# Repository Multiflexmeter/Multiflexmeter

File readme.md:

# Multiflexmeter V4
Frequent, low-cost and flexible measurements using the MultiFlexMeter. An Open-Source sensor platform.

## Documentation

- [Firmware Documentation](https://multiflexmeter.github.io/multiflexmeter)
- [Hardware specification](./docs/P22296-1-SPEC-2.0.pdf)
- [Firmware specification](./docs/P22296-10-SPEC-2.0.pdf)

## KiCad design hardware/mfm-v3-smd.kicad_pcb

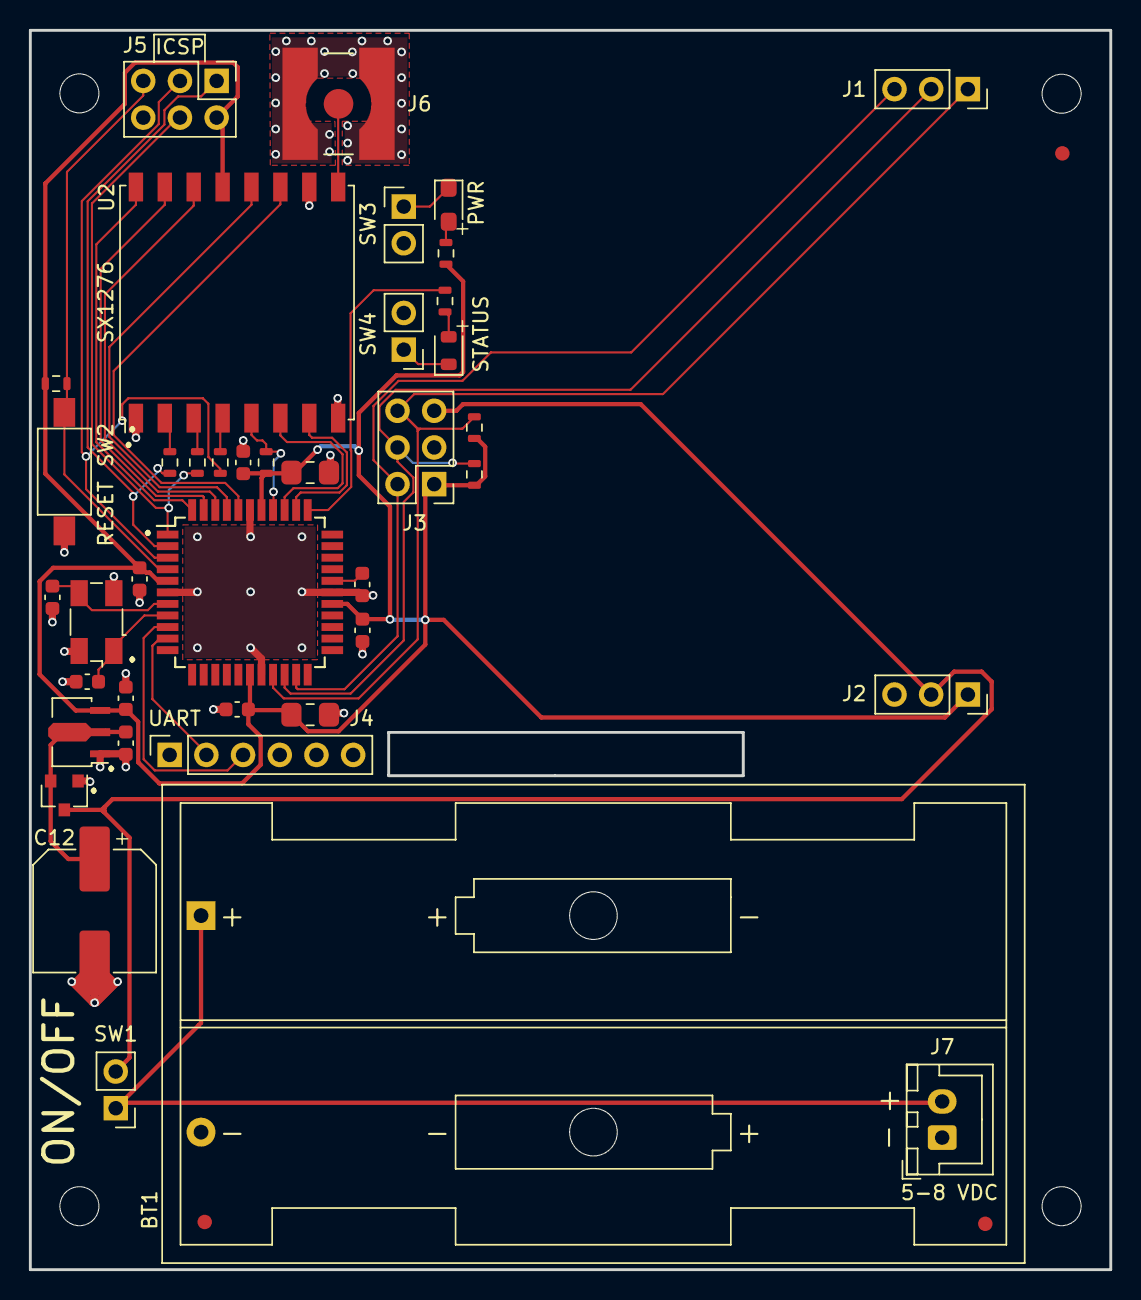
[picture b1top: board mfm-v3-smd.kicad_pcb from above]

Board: 2 copper layers, 74.8 x 85.8 mm, 47 parts (0 on the bottom side), 34 nets.

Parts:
BT1: Battery; BatteryHolder_Keystone_2462_2xAA
C1, C2: 2.2uF; C_0603_1608Metric
C3, C4, C6, C9, C11: 100nF; C_0603_1608Metric
C5, C10: 10uF; C_0805_2012Metric_GRM21BR61E106MA73L
C7, C8: 10pF; C_0603_1608Metric
C12: 820uF 16v; C_Elec_8x10.2
D1: LED_PWR; LED_0805_2012Metric_APT2012LSECK
D2: LED_STAT; LED_0805_2012Metric_APTD2012LQBC-D
FID1, FID2, FID3: Fiducial; Fiducial_1mm_Mask2mm
H1, H2, H3, H4: MountingHole; MountingHole_2.7mm_M2.5_DIN965
J1: MFM Module-Left; MFM_Module_Board_P123
J2: MFM Module-Right; PinSocket_1x03_P2.54mm_Vertical
J3: SMBUS Connector; PinHeader_2x03_P2.54mm_Vertical
J4: FTDI Connector; PinSocket_1x06_P2.54mm_Vertical
J5: ICSP Connector; PinHeader_2x03_P2.54mm_Vertical
J6: Antenna; LINX_CONSMA001-SMD-G
J7: JST Jack; JST_XH_B2B-XH-A_1x02_P2.50mm_Vertical
Q1: R.V. Protect; SOT-23
R1: 750R; R_0603_1608Metric_CRCW...C
R2, R5, R7, R8: 324R; R_0603_1608Metric_CRCW...C
R3, R4: 10k; R_0603_1608Metric_CRCW...C
R6, R9: 4k7; R_0603_1608Metric_CRCW...C
SW1: SW_VBAT; PinHeader_1x02_P2.54mm_Vertical
SW2: RESET; SW_SPST_PTS636
SW3: SW_LED_PWR; PinHeader_1x02_P2.54mm_Vertical
SW4: SW_LED_STAT; PinHeader_1x02_P2.54mm_Vertical
U1: MCP1703A-3302_SOT89; SOT-89-3_MCP1703
U2: LoRa_Radio; HOPERF_RFM9XW_SMD
U3: ATmega1284P-AU; TQFP-44_10x10mm_P0.8mm
Y1: 8MHz; Crystal_SMD_Abracon_ABM3B-4Pin_5.0x3.2mm

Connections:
+3V3: C2.2, C3.2, C4.2, C5.2, C6.2, C9.2, C10.1, J2.1, J3.1, J5.2, R1.1, R3.2, R4.2, R6.2, R9.2, U1.3, U2.13, U3.5, U3.17, U3.27, U3.38
AVR_MISO: J5.1, R8.1, U3.2
AVR_MOSI: J5.4, R7.1, U3.1
AVR_RX0: J4.3, U3.9
AVR_SCK: J5.3, R5.1, U3.3
AVR_TX0: J4.2, U3.10
GND: BT1.2, C1.1, C2.1, C3.1, C4.1, C5.1, C6.1, C7.1, C8.1, C9.1, C10.2, C11.1, C12.2, J2.3, J3.3, J4.6, J5.6, J6.2, J7.1, Q1.1, SW2.2, SW3.2, SW4.2, U1.1, U2.1, U2.8, U2.10, U3.6, U3.18, U3.28, U3.39, Y1.2, Y1.4
I2C_SCL: J1.1, J3.6, R9.1, U3.19
I2C_SDA: J1.2, J3.4, R6.1, U3.20
LED_STAT: R2.1, U3.34
NRST: J5.5, R4.1, SW2.1, U3.4
unnamed: BT1.1, J7.2, SW1.1
unnamed: C1.2, C12.1, Q1.2, U1.2
unnamed: C11.2, U3.29
unnamed: D1.1, SW3.1
unnamed: D1.2, R1.2
unnamed: D2.1, SW4.1
unnamed: D2.2, R2.2
unnamed: J6.1, U2.9
RADIO_DIO0: U2.14, U3.42
RADIO_DIO1: U2.15, U3.43
RADIO_DIO2: U2.16, U3.44
RADIO_DIO3: U2.11, U3.40
RADIO_DIO4: U2.12, U3.41
RADIO_DIO5: U2.7, U3.35
RADIO_NSS: R3.1, U2.5, U3.37
RADIO_RST: U2.6, U3.36
SMBALERT: J1.3, J3.2, U3.21
SPI_MISO: R8.2, U2.2
SPI_MOSI: R7.2, U2.3
SPI_SCK: R5.2, U2.4
VBAT: J2.2, J3.5, Q1.3, SW1.2
XTAL1: C7.2, U3.8, Y1.1
XTAL2: C8.2, U3.7, Y1.3

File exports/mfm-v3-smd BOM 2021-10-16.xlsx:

mfm-v3-smd
Quantity | Designator | Value | Footprint | Manufacturer | Manufacturer #
1 | BT1 | Battery | Battery:BatteryHolder_Keystone_2462_2xAA | Keystone | 2462
1 | C1 | 2.2uF | Capacitor_SMD:C_0603_1608Metric | TDK | C1608X7R1A225K080AE
1 | C2 | 2.2uF | Capacitor_SMD:C_0603_1608Metric | TDK | C1608X7R1A225K080AE
1 | C3 | 100nF | Capacitor_SMD:C_0603_1608Metric | TDK | C1608X7R1E104K080AA
1 | C4 | 100nF | Capacitor_SMD:C_0603_1608Metric | TDK | C1608X7R1E104K080AA
1 | C5 | 10uF | Capacitor_SMD:C_0805_2012Metric_GRM21BR61E106MA73L | Murata | GRM21BR61E106MA73L
1 | C6 | 100nF | Capacitor_SMD:C_0603_1608Metric | TDK | C1608X7R1E104K080AA
1 | C7 | 10pF | Capacitor_SMD:C_0603_1608Metric | Murata | GRT0335C1E100GA02D
1 | C8 | 10pF | Capacitor_SMD:C_0603_1608Metric | Murata | GRT0335C1E100GA02D
1 | C9 | 100nF | Capacitor_SMD:C_0603_1608Metric | TDK | C1608X7R1E104K080AA
1 | C10 | 10uF | Capacitor_SMD:C_0805_2012Metric_GRM21BR61E106MA73L | Murata | GRM21BR61E106MA73L
1 | C11 | 100nF | Capacitor_SMD:C_0603_1608Metric | TDK | C1608X7R1E104K080AA
1 | C12 | 820uF 16v | Capacitor_SMD:C_Elec_8x10.2 | <niet bestucken> | <niet bestucken>
1 | D1 | LED_PWR | custom_library_FP:LED_0805_2012Metric_APT2012LSECK | Kingbright | APT2012LSECK/J3-PRV
1 | D2 | LED_STAT | custom_library_FP:LED_0805_2012Metric_APTD2012LQBC-D | Kingbright | APTD2012LQBC/D
1 | J1 | MFM Module-Left | custom_library_FP:MFM_Module_Board_P123 | Preci-dip | 801-87-003-10-005101
1 | J2 | MFM Module-Right | Connector_PinSocket_2.54mm:PinSocket_1x03_P2.54mm_Vertical | Preci-dip | 801-87-003-10-005101
1 | J3 | SMBUS Connector | Connector_PinHeader_2.54mm:PinHeader_2x03_P2.54mm_Vertical | Preci-dip | 892-18-006-10-002101
1 | J4 | FTDI Connector | Connector_PinSocket_2.54mm:PinSocket_1x06_P2.54mm_Vertical | Preci-dip | 801-87-006-10-001101
1 | J5 | ICSP Connector | Connector_PinHeader_2.54mm:PinHeader_2x03_P2.54mm_Vertical | Preci-dip | 892-18-006-10-002101
1 | J6 | Antenna | custom_library_FP:LINX_CONSMA001-SMD-G | Linx Technologies | CONSMA001-SMD-G-T
1 | J7 | JST Jack | Connector_JST:JST_XH_B2B-XH-A_1x02_P2.50mm_Vertical | <niet bestucken> | <niet bestucken>
1 | Q1 | R.V. Protect | Package_TO_SOT_SMD:SOT-23 | Vishay | SI2315BDS-T1-E3
1 | R1 | 750R | custom_library_FP:R_0603_1608Metric_CRCW...C | Vishay | CRCW0603750RFKEAC
1 | R2 | 324R | custom_library_FP:R_0603_1608Metric_CRCW...C | Vishay | CRCW0603324RFKEA
1 | R3 | 10k | custom_library_FP:R_0603_1608Metric_CRCW...C | Vishay | RCC060310K0FKEA
1 | R4 | 10k | custom_library_FP:R_0603_1608Metric_CRCW...C | Vishay | RCC060310K0FKEA
1 | R5 | 324R | custom_library_FP:R_0603_1608Metric_CRCW...C | Vishay | CRCW0603324RFKEA
1 | R6 | 4k7 | custom_library_FP:R_0603_1608Metric_CRCW...C | Vishay | RCC06034K70FKEA
1 | R7 | 324R | custom_library_FP:R_0603_1608Metric_CRCW...C | Vishay | CRCW0603324RFKEA
1 | R8 | 324R | custom_library_FP:R_0603_1608Metric_CRCW...C | Vishay | CRCW0603324RFKEA
1 | R9 | 4k7 | custom_library_FP:R_0603_1608Metric_CRCW...C | Vishay | RCC06034K70FKEA
1 | SW1 | SW_VBAT | Connector_PinHeader_2.54mm:PinHeader_1x02_P2.54mm_Vertical | Preci-dip | 800-10-002-10-002101
1 | SW2 | RESET | custom_library_FP:SW_SPST_PTS636 | C&K | PTS636 SM43 SMTR LFS
1 | SW3 | SW_LED_PWR | Connector_PinHeader_2.54mm:PinHeader_1x02_P2.54mm_Vertical | Preci-dip | 800-10-002-10-002101
1 | SW4 | SW_LED_STAT | Connector_PinHeader_2.54mm:PinHeader_1x02_P2.54mm_Vertical | Preci-dip | 800-10-002-10-002101
1 | U1 | MCP1703A-3302_SOT89 | custom_library_FP:SOT-89-3_MCP1703 | Microchip Technology | MCP1703AT-3302E/MB
1 | U2 | LoRa_Radio | RF_Module:HOPERF_RFM9XW_SMD | NiceRF | SX1276-Module
1 | U3 | ATmega1284P-AU | Package_QFP:TQFP-44_10x10mm_P0.8mm | Microchip Technology / Atmel | ATMEGA1284P-AUR
1 | Y1 | 8MHz | Crystal:Crystal_SMD_Abracon_ABM3B-4Pin_5.0x3.2mm | ABRACON | ABM3B-8.000MHZ-10-1-U-T

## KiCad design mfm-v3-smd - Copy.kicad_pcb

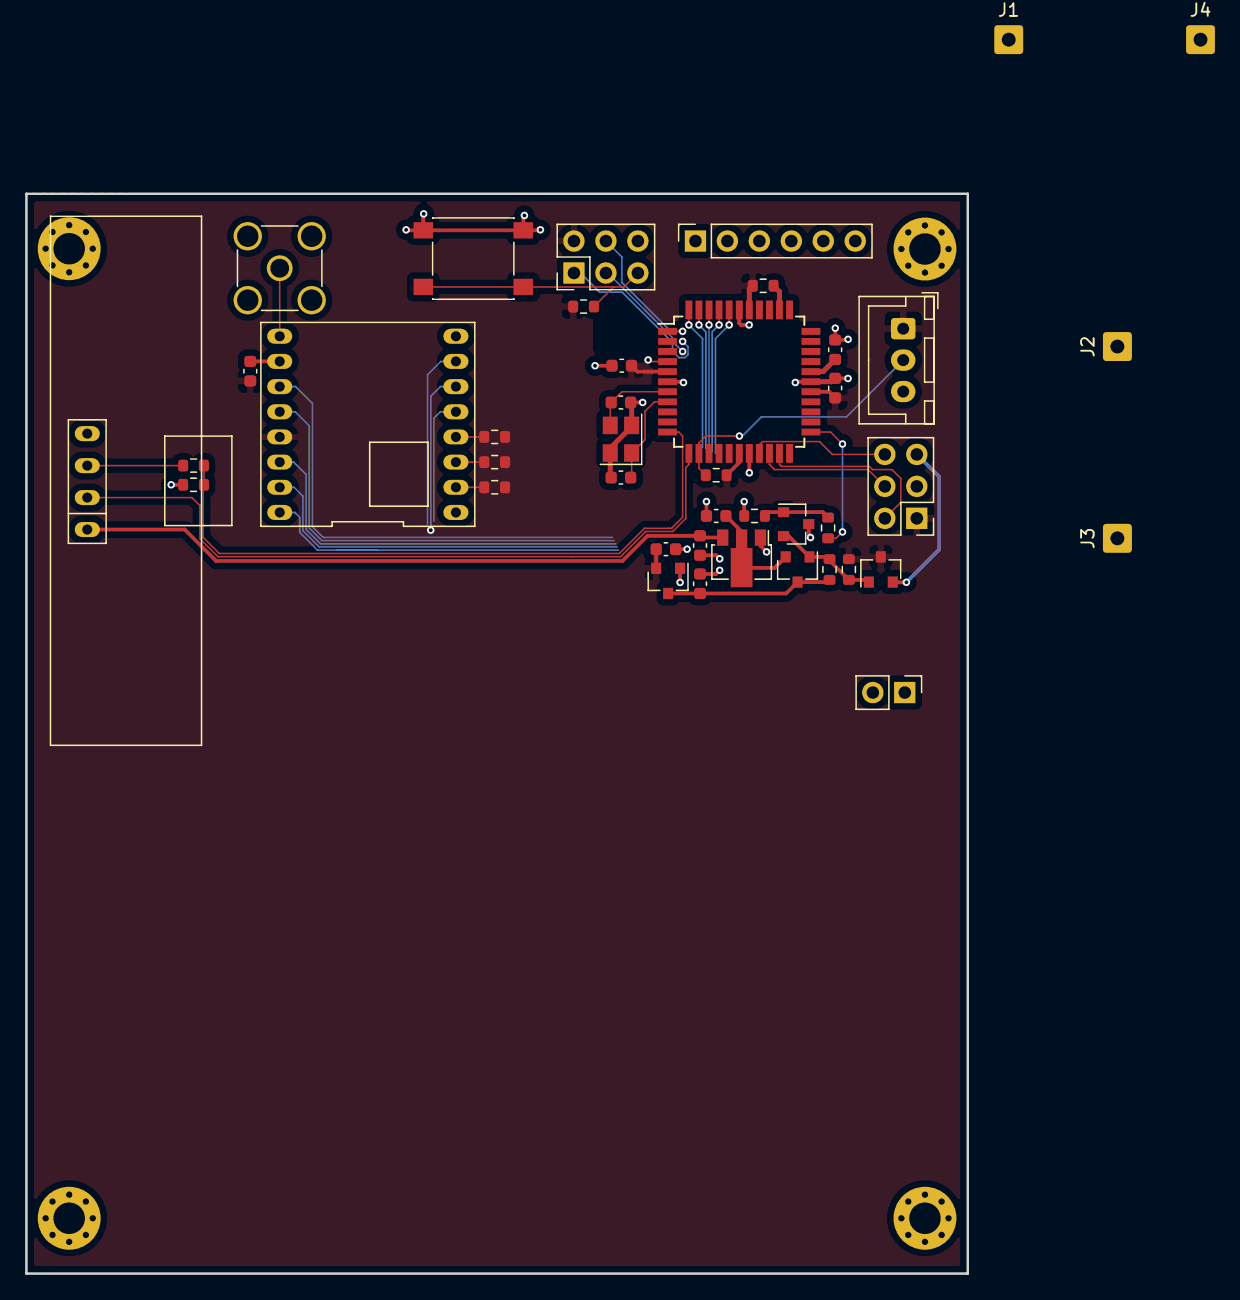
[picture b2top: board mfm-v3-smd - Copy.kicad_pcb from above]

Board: 2 copper layers, 74.8 x 85.8 mm, 46 parts (0 on the bottom side), 39 nets.

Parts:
C1, C2: 1u; C_0603_1608Metric
C3, C4, C5: 10u; C_0603_1608Metric
C7, C8: 12p; C_0603_1608Metric
C9, C10, C11: 100n; C_0603_1608Metric
H1, H2, H3, H4: MountingHole_Pad; MountingHole_2.5mm_Pad_Via
J1: B-; SolderWire-0.5sqmm_1x01_D0.9mm_OD2.3mm
J2, J3: Serie; SolderWire-0.5sqmm_1x01_D0.9mm_OD2.3mm
J4: B+; SolderWire-0.5sqmm_1x01_D0.9mm_OD2.3mm
J7, J10: Conn_02x03_Odd_Even; PinHeader_2x03_P2.54mm_Vertical
J8: Conn_01x03; JST_XH_B3B-XH-A_1x03_P2.50mm_Vertical
J11: Ultrasone; JSN-SR04T
J12: Conn_01x06; PinSocket_1x06_P2.54mm_Vertical
J13: Antenna; SMA_Amphenol_901-144_Vertical
Q1, Q2: PMOS; SOT-23
Q3: NMOS; SOT-23
R1: 4k7; R_0603_1608Metric
R2, R3, R10, R11, R14: 10k; R_0603_1608Metric
R4: 100; R_0603_1608Metric
R5, R7, R8: 330; R_0603_1608Metric
R6: 1k8; R_0603_1608Metric
R9: 3k3; R_0603_1608Metric
SW1: SW_VBAT; PinHeader_1x02_P2.54mm_Vertical
SW2: SW_NRST; SW_Push_1P1T_NO_6x6mm_H9.5mm
U1: 3.3V LDO; SOT-23
U2: 5V LDO; SOT-89-3
U4: LoRa_Radio; RFM95
U5: ATmega1284P-AU; TQFP-44_10x10mm_P0.8mm
Y1: 16MHz; Crystal_SMD_3225-4Pin_3.2x2.5mm

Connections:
+3.3V_SW: J7.5, Q2.2
+3V3: C2.2, C5.2, C9.2, C10.1, J7.1, J8.1, J10.2, Q2.3, R1.2, R3.2, R10.2, R11.2, U1.2, U4.13, U5.5, U5.17, U5.27, U5.38
+5V_SW: C4.2, J11.1, U2.3
AVR_MISO: J10.1, R8.1, U5.2
AVR_MOSI: J10.4, R7.1, U5.1
AVR_RX0: J12.3, U5.9
AVR_RX1: R6.1, R9.2, U5.11
AVR_SCK: J10.3, R5.1, U5.3
AVR_TX0: J12.2, U5.10
AVR_TX1: J11.2, U5.12
GND: C1.1, C2.1, C3.1, C4.1, C5.1, C7.1, C8.1, C9.1, C10.2, C11.1, J1.1, J7.3, J8.3, J10.6, J11.4, J12.6, J13.2, Q3.3, R9.1, R14.1, SW2.2, U1.1, U2.1, U4.1, U4.8, U4.10, U5.6, U5.18, U5.28, U5.39, Y1.2, Y1.4
I2C_SCL: J7.6, U5.19
I2C_SDA: J7.4, U5.20
NRST: J10.5, R10.1, SW2.1, U5.4
unnamed: C3.2, Q1.2, U2.2
unnamed: C11.2, U5.29
unnamed: J2.1, J3.1
unnamed: J11.3, R6.2
unnamed: J13.1, U4.9
unnamed: Q1.1, Q2.1, Q3.2, R2.1, R3.1
unnamed: Q3.1, R4.2, R14.2
ONEWIRE: J8.2, R1.1, U5.13
RADIO_DIO0: U4.14, U5.42
RADIO_DIO1: U4.15, U5.41
RADIO_DIO2: U4.16, U5.40
RADIO_DIO3: U4.11, U5.44
RADIO_DIO4: U4.12, U5.43
RADIO_DIO5: U4.7, U5.37
RADIO_NSS: R11.1, U4.5, U5.35
RADIO_RST: U4.6, U5.36
SMBALERT: J7.2, U5.21
SPI_MISO: R5.2, U4.2
SPI_MOSI: R7.2, U4.3
SPI_SCK: R8.2, U4.4
SW_PERIF: R4.1, U5.23
VBAT: J4.1, SW1.1
VBAT_SW: C1.2, Q1.3, R2.2, SW1.2, U1.3
XTAL1: C7.2, U5.8, Y1.1
XTAL2: C8.2, U5.7, Y1.3

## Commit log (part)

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2023-12-19 change: add functions for up/down frame counters.
2023-12-19 fix: wrong function was used in commit cbe92665b319ef2df65c9623bddbb77740f940f2
2023-12-19 change: do not devnonce counter, but up frame counter.
2023-12-19 change: add timeout to hanging states.
2023-12-19 change: set current protocol version and version number.
2023-12-19 change: implement read sensor module information
2023-12-19 change: fix must be ID + 1.
2023-12-21 change: add some am1805 RTC functions to configure some registers and functions
2023-12-21 change: print debug status of registers
2023-12-21 fix: wrong register and value used by mistake.
2023-12-21 change: cleanup testcode
2023-12-21 change: add work around for WDI pulse at entering sleepmode.
2023-12-21 change: add functions for get control1 and control2 register.
2023-12-21 change: add function to get ex1 and ex2 irq status.
2023-12-21 change: handling USB attached, no off mode.
2023-12-21 change: reset at new measurement (new interval)
2023-12-21 change: add detect previous alarm
2023-12-22 change: preset MainPeriodSleep on Lora interval.
2023-12-22 change: rewrite of found a previous alarm time.
2023-12-27 change: add documentation file
2023-12-27 change: add app file to doxyfile settings
2023-12-27 change: add image path to doxyfile
2023-12-27 change: add some doxygen documentation
2023-12-27 change: add function to get Temperature from controller.
2023-12-27 fix: read vref supply, not only adc value.
2023-12-27 change: convert battery gauge temperature measurement.
2023-12-28 change: add null terminator for SW version.
2023-12-28 change: add printing battery capacity
2023-12-28 change: extra guard on valid values.
2023-12-28 change: add inlcude FRAM functions.
2023-12-28 change: remove unused weak functions, not needed anymore because of include.
2023-12-28 change: guard different reserved segments.
2023-12-29 change: update doxygen documentation.
2023-12-29 change: rewrite saveBatteryEos() and getBatteryEos() with struct/union and add supply.
2023-12-29 change: add reboot command
2023-12-29 change: add command to enable/disable testmode
2023-12-29 change: add new files for productiontestTask
2023-12-29 change: fix for resuming task. Just SetPeriod not enought to retrigger the task.
2023-12-29 change: implement of return value of I/O expander.
2023-12-29 change: make I/O expander names more clear.
2023-12-29 change: add testing function for test VSYS is available, based on the external pullup resistors on the SPI lines.
2023-12-29 change: add testing vSys switching.
2023-12-29 change: make helper functions for print okay and failed.
2023-12-29 change: add productiontest I/O expander sensor
2024-01-11 change: cubeMx file change for switch arround usart 1 and 2.
2024-01-11 change: enable Exti interrupt in CubeMx file
2024-01-12 change: modify cubeMx manual, has no consequence for code generation.
2024-01-12 change: modify handling when no sensor is active.
2024-01-16 Move to subfolder
2024-01-16 change: check on control characters and 0xff to return a empty string.
2024-01-17 change: make sure EX2P and EX1P bits are used as set before.
2024-01-17 change: fix of sleeptime when no active sensor is found. Must be one day of secondes.
2024-01-18 Fix: century and month conversion corrected. Also add some comment for conversion.
2024-01-18 change: save sensorModuleEnabled in FRAM.
2024-01-18 change: use FRAM setting instead.
2024-01-18 change: enable orange LED at TX transmit.
2024-01-18 change: add functions for enable / disable supercap
2024-01-22 change: add serial command to force sleep.
2024-01-22 change: add print debug info of control SC.
2024-01-23 change: add test command Set+Test=7,8 for a forced measurement send by LoRa
2024-01-23 change: add new sensor command initialize sensor module
2024-01-23 change: add set/get function for forced sensor init.
2024-01-23 change: fix on 9a952cf5b2ffc4dcea254f8a2445d6caf4df0a26
2024-01-24 change: update of state diagram of maintask.
2024-01-24 change: correction of mistake in debug text.
2024-01-24 change: only proceed when HAL_OK, all other HAL error use return I2C_TIMEOUT.
2024-01-25 Change: print also fields slotId, Protocol and datasize.
2024-01-25 change: rename function getMeasureTime() -> getNumberOfSamples()
2024-01-25 fix: updated corrupted document.
2024-01-26 change: add diagnostic bits to FRAM struct.
2024-01-26 change: split up ext wakeup. Also move USB from ext2 to ext1.
2024-01-26 change: save diagnostic (first 8 bits) in MFM basedata and send it in the messagetype (0x01 and 0x02).
2024-01-26 fix: add missing copy of MFM base data from measurement to dataflash.
2024-01-26 change: add missing set true of valid TX action.
2024-01-29 change: add CRC check to FRAM settings struct.
2024-01-30 change: make sure that after change of DevEu, AppKey and JoinId the settings are stored in NVM, rejoin flag is set and reboot is exectued.
2024-01-30 change: make sure rejoin is also triggered when USB is attached.
2024-01-30 change: add function to stop Join.
2024-01-30 change: preset all keys on new value, will be updated at join.
2024-02-01 change: Call deinit/init after HAL error. Prevents short freezing SCL lines after a HAL error.
2024-02-08 change: enable hex/bin build, set optimize on speed.
2024-02-09 change: add option for mode for init battery gauge.
2024-02-14 change: detect a double reset within 5 seconds to force a rejoin
2024-02-14 change: add wakeup detection function
2024-02-14 change: add comment to getResetSource().
2024-02-14 change: rewrite debug line for forced rejoin.
2024-02-14 change: softwareVersion to 0.1.01
2024-02-14 change: rewrite print function to helper function
2024-02-15 change: add new command to force an EOS measurement.
2024-02-20 change: make sure all data can be read including the CRC.
2024-02-21 change: fix correct wrong PIN for LED2.
2024-02-21 change: move enable orange LED to mainTask. In LoraApp toggle doesn't work, because task switch is not done between.
2024-02-21 change: enable orange LED at rejoin also.
2024-02-21 change: correct blinking times for LED
2024-02-21 change: make sure led toggle/blink always start with ON cycle.
2024-02-21 change: softwareVersion to 0.1.03
2024-02-21 change: also set alarmtime in USB connected mode.
2024-02-22 change: temporary add some debug printing
2024-02-22 change: temporary debug print for DevNonce check.
2024-02-22 change: add debug printing for SPI timeouts for FRAM read/write operations.
2024-02-22 change: some expiremental testcode
2024-02-22 Revert "change: temporary debug print for DevNonce check."
    This reverts commit 2bc55f9d5210bfaf0989fe50bbac6cfee801868c.
2024-02-22 change: softwareVersion to 0.1.05
2024-02-22 change: add function to print JoinNonce
2024-02-22 change: modify layout of debug print
2024-02-23 change: rewrite state SWITCH_SENSOR_SLOT when no Sensor slots are active flow part 1.
2024-02-23 change: rewrite to send data also when no sensor is configured.
2024-02-23 change: add weak functions to commConfig.c
2024-02-23 change: softwareVersion to 0.1.08
2024-02-26 change: softwareVersion to 0.1.09
2024-02-27 change: testcode to catch "no_active_command" status.
2024-02-27 Revert "change: temporary testcode for periodically fast test measuring"
    This reverts commit 27da65a9534f5f9d4f23a65b3d29085912a2a266.
2024-02-27 change: softwareVersion to 0.1.10
2024-02-27 change: add numberOfSensorModule
2024-02-27 change: set new interval based on same round or not.
2024-02-27 change: use function for get next interval.
2024-02-28 change: make test define for equal interval between measurements.
    Normally define SEND_MEASUREMENT_IN_EQUAL_INTERVAL must be disabled.
    Then each sensormodule measurements is send with interval of 1 minute between each module.
    After all sensors are send, then the LoraInterval - minus elapsed time is used.
2024-02-28 Revert "change: disable test define SEND_MEASUREMENT_IN_EQUAL_INTERVAL"
    This reverts commit 276c89b665b654105ada60c661af1cf7dfc37e1f.
2024-02-28 change: add some helper function to print debug lines with layout.
2024-02-28 change: move printCounters()
2024-02-28 change: make more readable debug print for printSensorModulePressur() data
2024-02-28 change: mixed up order of TimeTrace and VerboseLevel
2024-02-28 change: use verboseLevel variable in function
2024-02-28 change: print verboseLevel M for printSensorModulePressure
2024-02-28 change: use verboseLevel variable in getWakeupSource() function
2024-02-28 change: rewrite of getWakeupResource for better readable layout
2024-02-28 change: softwareVersion to 0.1.11
2024-02-28 change: remove library warning, user defined pins is done.
2024-03-04 change: enable VSYS for detecting INTx 1-6 cause. Only debug printing.
2024-03-04 change: make sure Ex2 wakeup is skipped, if ex1 is active. Because of pulse given from IC AM1805 itself.
2024-03-04 change: print MFM base data to measurement data
2024-03-05 feat(smbus): add block_write
2024-03-05 chore(formatting): Format using clang-format
2024-03-05 fix(ci): checkout submodules
2024-03-06 change: add some temporary test code for evaluating result of init.
2024-03-06 change: add sensor init failed to diagnostic data for channel 1 and channel 2.
2024-03-06 Revert "change: add temporary test code for periodically start forced init."
    This reverts commit 27df02df3374f9f3bfae70a5f4ad8bbda634f1d9.
2024-03-06 Revert "change: add some temporary test code for evaluating result of init."
    This reverts commit 7f451888f75901a3b00ea6ab01211f052ad3347c.
2024-03-06 change: softwareVersion to 0.1.12
2024-03-06 change: add function to detect a change in interval.
2024-03-07 change: only change appKey when this is realy changed. Otherwise the active join is not valid anymore.
2024-03-07 change: update debug print for HUBA sensormodule with rough values.
2024-03-07 change: add command to enable slot1 power, for programming sensor board.
2024-03-07 change: softwareVersion to 0.1.14
2024-03-11 change: add revision information
2024-03-11 change: fix some doxygen warnings
2024-03-13 change: add new image folder.
2024-03-13 change: make ESD message RED.
2024-03-14 change: remove unused function stop_mainTask().
2024-03-14 change: rewrite routine getNextMeasureInterval() too make sure all situation are catched
2024-03-14 change: prevent hanging in while(1) at sleep, prevent with reset of system.
2024-04-01 fix: use tagged version in defines
2024-04-02 change: add debug print wrong VSYS setting
2024-04-02 change: add debug print vsys verify in sate where hanging starts.
2024-04-02 change: split up Nonce command Get+Nonce
2024-04-02 change: add downlink command set interval
2024-04-02 change: softwareVersion to 0.1.18
2024-04-02 change: enable iwdg, code generation of cubeMx config file change
2024-04-02 change: add function to reset watchdog
2024-04-02 change: add variant of function for dataflash wait on ready with timeout
2024-04-02 change: normal printf changed to APP_LOG().
2024-04-03 Fix: correct mistake in get+Sample, add missing senosr ID in return message
2024-04-04 change: also init HAL I2C in productiontestTask, otherwise it could fail.
2024-04-04 change: add retry for I2C I/O expander.
2024-04-05 change: add bit4 (0x10) for trigger sensor initialization with a rejoin.
2024-04-05 change: increase watchdog from prescaler 64 to 128.
2024-04-05 change: softwareVersion to 0.1.21
2024-04-05 change: enable bits in FRAM struct also, to trigger forced sensor init next round.
2024-04-08 change: add checking on I2C error, try to repair. Otherwise reboot.
2024-04-09 change: correct I2C var. By mistake copy of ch 1, must be ch 2.
2024-04-22 change: add function to indicate a new battery is placed.
2024-04-22 change: correcting tag <h2>
2024-04-25 change: softwareVersion to 0.1.24
2024-06-19 chore: Add hardware from release
2024-06-19 ci(doxygen): add doxygen build and publish workflow
2024-06-19 ci(doxygen): add permissions
2024-07-30 Update readme and pdf name
2024-10-31 update sources to 0.2.05 w/ i2c var read patch
2024-11-08 feat: 0x57 DL set DR command
2025-04-16 docs: rename borehole to well
2025-04-24 docs: update spec filenames
